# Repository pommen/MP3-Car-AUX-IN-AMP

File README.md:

# MP3 Car AUX IN AMP
A simple pre amp to boost teh shitty signal from a MP3 player to match a car aux-in levels

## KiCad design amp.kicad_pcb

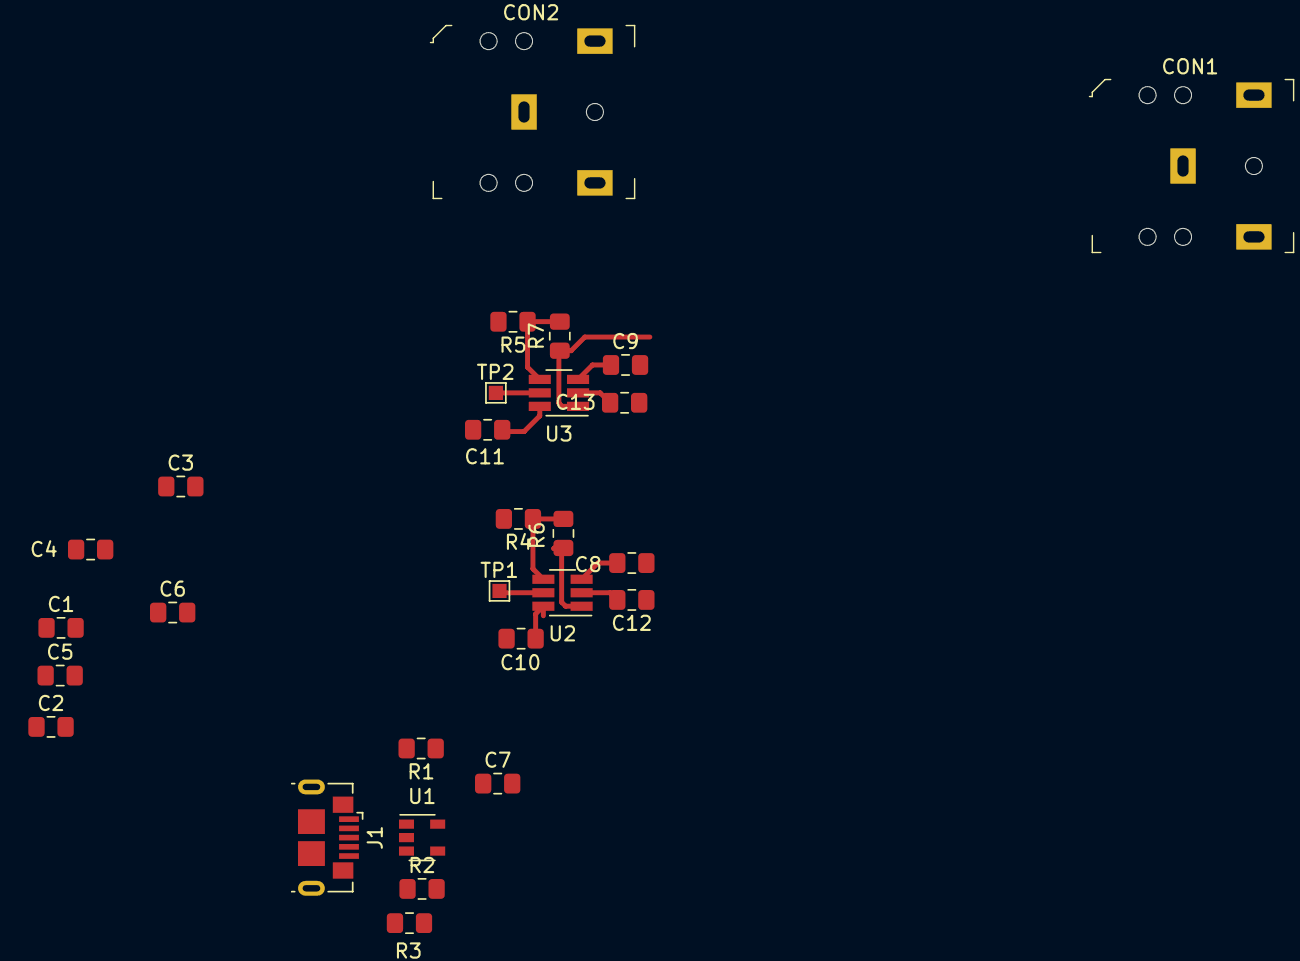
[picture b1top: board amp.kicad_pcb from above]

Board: 2 copper layers, 28 parts (0 on the bottom side), 15 nets.

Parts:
C1, C2: 1u; C_0805_2012Metric_Pad1.15x1.40mm_HandSolder
C3, C4, C7, C8, C9: 100n; C_0805_2012Metric_Pad1.15x1.40mm_HandSolder
C5, C6, C10, C11, C12, C13: 10n; C_0805_2012Metric_Pad1.15x1.40mm_HandSolder
CON1, CON2: SJ1-3523N; Headphone_Jack_2.5mm_SJ1-3523N
J1: USB_B_Mini; USB_Micro-B_GCT_USB3076-30-A
R1, R2: 100K; R_0805_2012Metric_Pad1.15x1.40mm_HandSolder
R3: 280R; R_0805_2012Metric_Pad1.15x1.40mm_HandSolder
R4, R5, R6, R7: R; R_0805_2012Metric_Pad1.15x1.40mm_HandSolder
TP1: ShutdownL; TestPoint_Pad_1.0x1.0mm
TP2: ShutdownR; TestPoint_Pad_1.0x1.0mm
U1: LM321; SOT-23-5
U2, U3: LTC6246IS6; SOT-23-6_Handsoldering

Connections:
+2V5: C1.1, C3.1, C5.1, C7.1, C10.1, C11.1, J1.1, R1.1, U1.5, U2.6, U3.6
-2V5: C2.2, C4.2, C6.2, C7.2, C12.2, C13.2, J1.5, R2.2, U1.2, U2.2, U3.2
GND: C1.2, C2.1, C3.2, C4.1, C5.2, C6.1, C10.2, C11.2, C12.1, C13.1, CON1.1, CON2.1, R3.1, R4.2, R5.2
unnamed: C8.1, U2.3
unnamed: C9.1, U3.3
unnamed: R1.2, R2.1, U1.1
unnamed: R3.2, U1.3, U1.4
unnamed: R4.1, R6.2, U2.4
unnamed: R5.1, R7.2, U3.4
unnamed: TP1.1, U2.5
unnamed: TP2.1, U3.5
inL: C8.2, CON1.2
inR: C9.2, CON1.3
outL: CON2.2, R6.1, U2.1
outR: CON2.3, R7.1, U3.1

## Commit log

2018-09-05 description
